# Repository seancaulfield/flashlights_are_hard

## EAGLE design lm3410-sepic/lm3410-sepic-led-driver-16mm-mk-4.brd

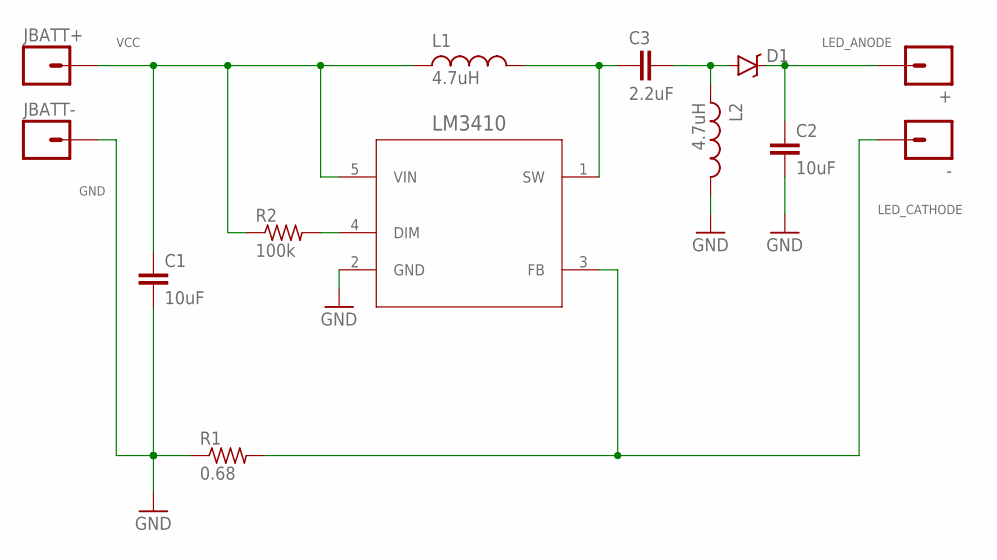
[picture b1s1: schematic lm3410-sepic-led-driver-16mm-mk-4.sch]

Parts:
+: M01PTH-1.2MM; 1X01-1.2MM
-: M01PTH-1.2MM-NS; 1X01-1.2MM-NS
C1, C2: 10uF; C0603
C3: 2.2uF; C0805
D1: MBRA140; SMA-DIODE
JBATT+: M01NOT-A-VIA-NOPE; 1X01_NOSILK_NOSTOP
JBATT-: M01NOT-A-VIA-NOPE; 1X01_NOSILK_NOSTOP
L1, L2: 4.7uH; TAIYO-YUDEN-30XX
LM3410: LM3410XMF; SOT95P285X120-5N
R1: 0.68; R1206
R2: 100k; R0603

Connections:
GND: C1.2, C2.2, JBATT-.P$1, L2.2, LM3410.2 (GND), R1.1
LED_ANODE: +.P$1, C2.1, D1.C
LED_CATHODE: -.P$1, LM3410.3 (FB), R1.2
unnamed: C3.2, D1.A, L2.1
unnamed: LM3410.4 (DIM), R2.2
SW: C3.1, L1.2, LM3410.1 (SW)
VCC: C1.1, JBATT+.P$1, L1.1, LM3410.5 (VIN), R2.1

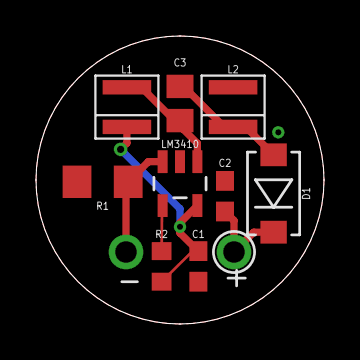
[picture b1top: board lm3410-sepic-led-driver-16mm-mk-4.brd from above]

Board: 2 copper layers, 16.0 x 16.0 mm, 13 parts (0 on the bottom side), 7 nets.

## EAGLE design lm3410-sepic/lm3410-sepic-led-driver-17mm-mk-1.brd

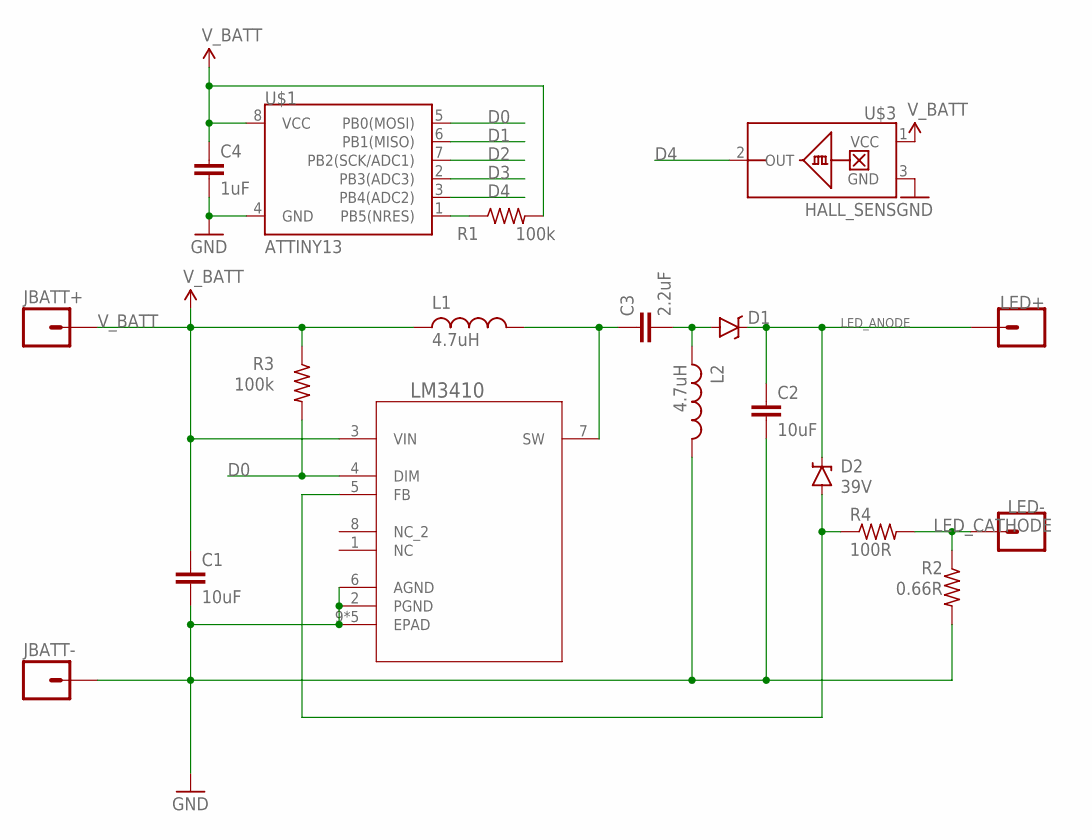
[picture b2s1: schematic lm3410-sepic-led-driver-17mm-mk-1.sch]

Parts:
C1, C2: 10uF; C0805
C3: 2.2uF; C0805
C4: 1uF; C0603
D1: BAT20J; SOD-323
D2: 39V; SOD-323
JBATT+: M01NOT-A-VIA-NOPE; 1X01_NOSILK_NOSTOP
JBATT-: M01NOT-A-VIA-NOPE; 1X01_NOSILK_NOSTOP
L1, L2: 4.7uH; TAIYO-YUDEN-30XX
LED+: M01PTH-NS-NOTSUCK; 1X01NSATALL
LED-: M01PTH-NS-NOTSUCK; 1X01NSATALL
R1, R3: 100k; R0603
R2: 0.66R; R1206
R4: 100R; R0603
U1: LM3410; SOP65P490X110-9N-A
U$1: ATTINY13; SO08
U$3: HALL_SENS; SOT23-3

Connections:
D0: R3.2, U1.4 (DIM), U$1.5 (PB0(MOSI))
D1: U$1.6 (PB1(MISO))
D2: U$1.7 (PB2(SCK/ADC1))
D3: U$1.2 (PB3(ADC3))
D4: U$1.3 (PB4(ADC2)), U$3.2 (OUT)
GND: C1.2, C2.2, C4.2, JBATT-.P$1, L2.2, R2.2, U1.2 (PGND), U1.6 (AGND), U1.9 (EPAD), U1.9@1 (EPAD), U1.9@2 (EPAD), U1.9@3 (EPAD), U1.9@4 (EPAD), U$1.4 (GND), U$3.3 (GND)
LED_ANODE: C2.1, D1.C, D2.C, LED+.1
LED_CATHODE: LED-.1, R2.1, R4.2
unnamed: C3.2, D1.A, L2.1
unnamed: R1.1, U$1.1 (PB5(NRES))
unnamed: D2.A, R4.1, U1.5 (FB)
SW: C3.1, L1.2, U1.7 (SW)
V_BATT: C1.1, C4.1, JBATT+.P$1, L1.1, R1.2, R3.1, U1.3 (VIN), U$1.8 (VCC), U$3.1 (VCC)

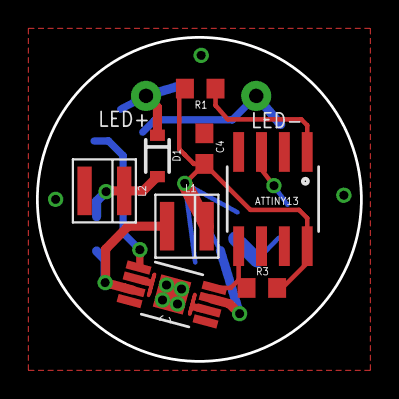
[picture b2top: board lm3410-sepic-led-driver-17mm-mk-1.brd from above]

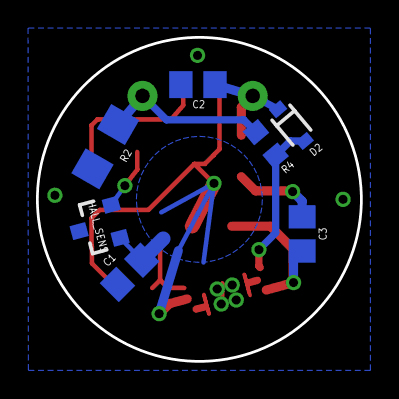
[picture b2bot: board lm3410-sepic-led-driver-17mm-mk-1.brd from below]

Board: 2 copper layers, 18.0 x 18.0 mm, 19 parts (8 on the bottom side), 10 nets.

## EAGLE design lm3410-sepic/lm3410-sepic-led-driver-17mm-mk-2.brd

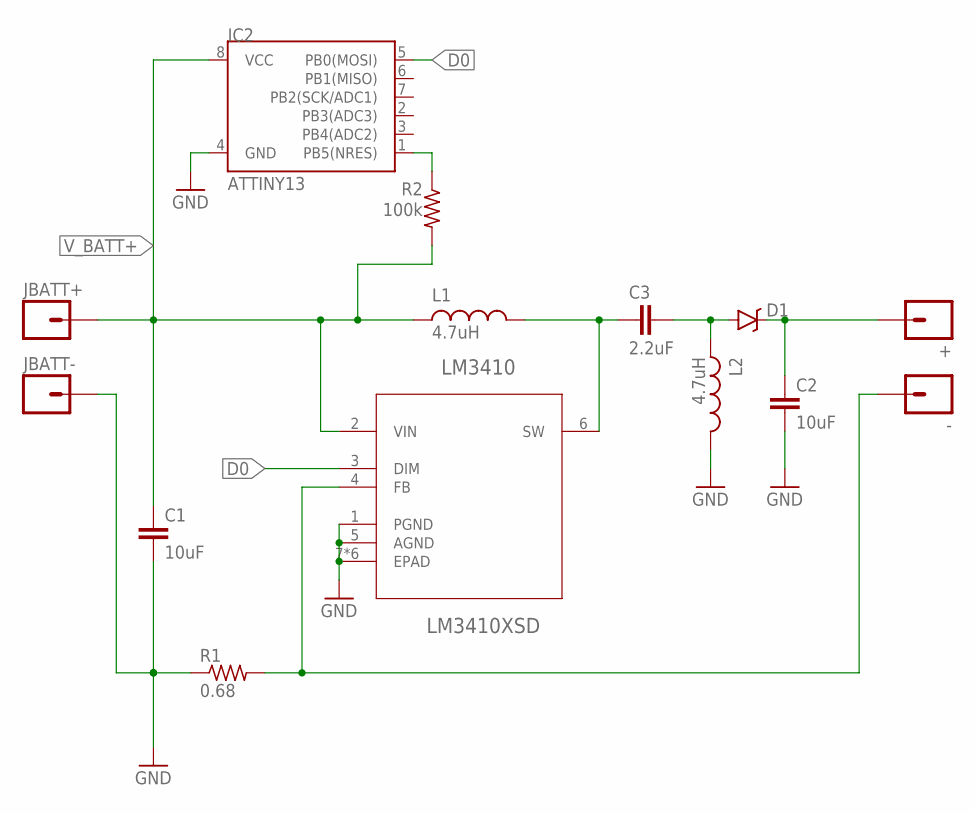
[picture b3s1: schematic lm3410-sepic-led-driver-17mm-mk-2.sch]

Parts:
+: M01PTH-KIT; 1X01-KIT
-: M01NOSILK-KIT; 1X01NS-KIT
C1, C2: 10uF; C0603
C3: 2.2uF; C0805
D1: BAT20J; SOD-323
IC2: ATTINY13; SO08
JBATT+: M01NOT-A-VIA-NOPE; 1X01_NOSILK_NOSTOP
JBATT-: M01NOT-A-VIA-NOPE; 1X01_NOSILK_NOSTOP
L1, L2: 4.7uH; INDUCTOR_2X1.6MM
LM3410: LM3410XSD; DFN300X300X80-7N
R1: 0.68; R1206
R2: 100k; R0402

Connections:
D0: IC2.5 (PB0(MOSI)), LM3410.3 (DIM)
GND: C1.2, C2.2, IC2.4 (GND), JBATT-.P$1, L2.P$2 (2), LM3410.1 (PGND), LM3410.5 (AGND), LM3410.7 (EPAD), LM3410.7@1 (EPAD), LM3410.7@2 (EPAD), LM3410.7@3 (EPAD), LM3410.7@4 (EPAD), LM3410.7@5 (EPAD), R1.1
LED_ANODE: +.1, C2.1, D1.C
unnamed: C3.2, D1.A, L2.P$1 (1)
unnamed: IC2.1 (PB5(NRES)), R2.1
unnamed: -.1, LM3410.4 (FB), R1.2
SW: C3.1, L1.P$2 (2), LM3410.6 (SW)
V_BATT+: C1.1, IC2.8 (VCC), JBATT+.P$1, L1.P$1 (1), LM3410.2 (VIN), R2.2

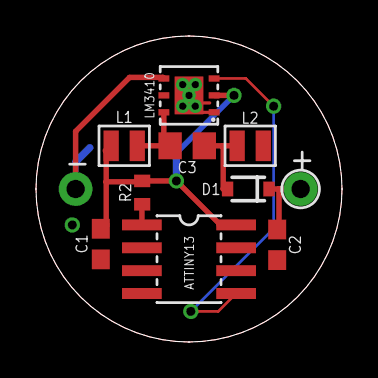
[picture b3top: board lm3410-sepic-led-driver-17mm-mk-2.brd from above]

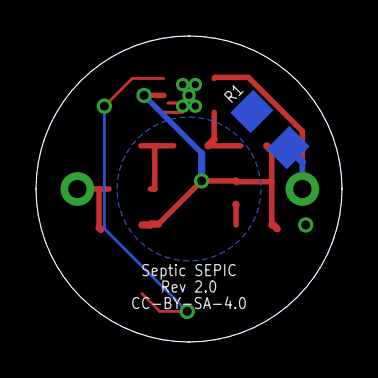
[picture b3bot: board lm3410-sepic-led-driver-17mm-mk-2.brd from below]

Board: 2 copper layers, 17.0 x 17.0 mm, 14 parts (2 on the bottom side), 8 nets.

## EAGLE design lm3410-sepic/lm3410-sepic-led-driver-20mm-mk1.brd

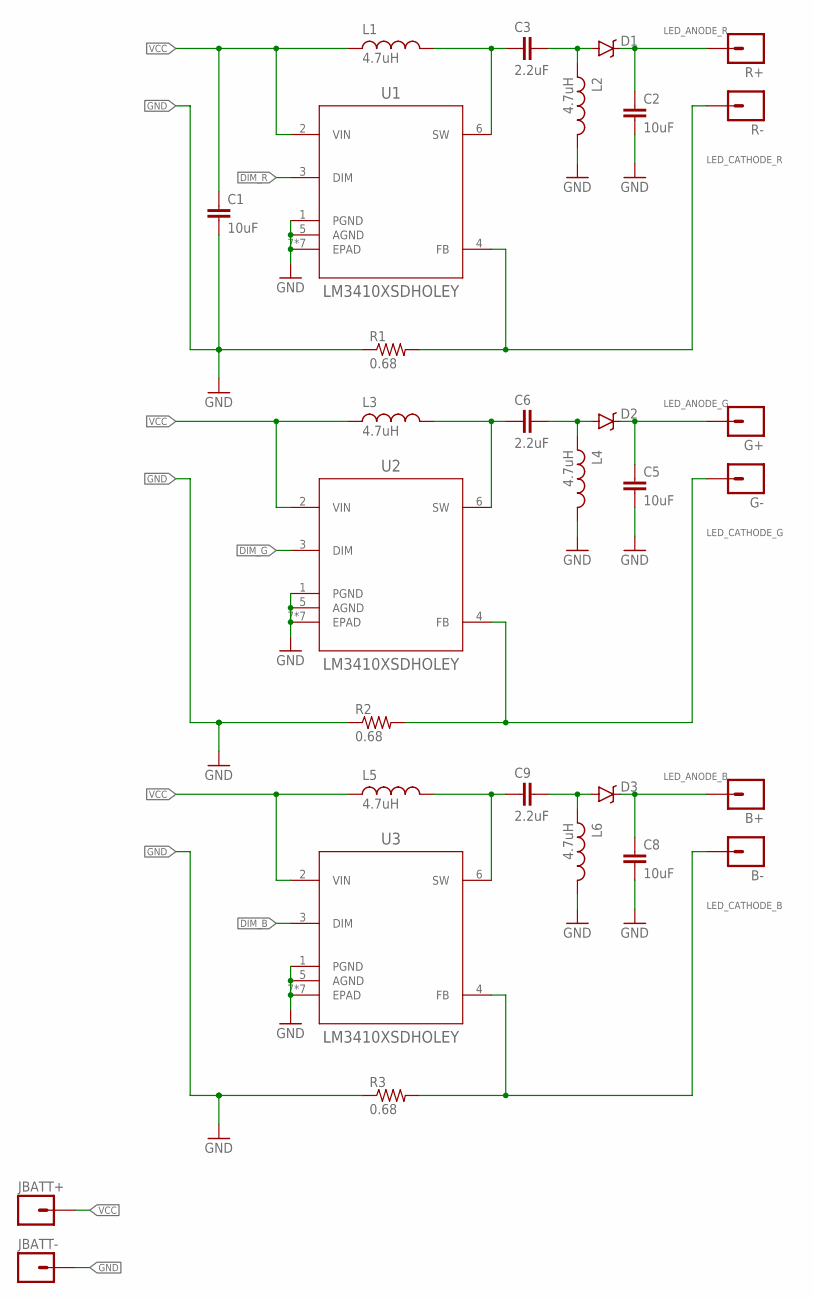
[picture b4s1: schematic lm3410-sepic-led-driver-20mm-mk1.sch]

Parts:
B+: M01PTH-1.2MM; 1X01-1.2MM
B-: M01PTH-1.2MM-NS; 1X01-1.2MM-NS
C1, C2, C5, C8: 10uF; C0603
C3, C6, C9: 2.2uF; C0805
D1, D2, D3: PMEG4005EJ; SOD-323
G+: M01PTH-1.2MM; 1X01-1.2MM
G-: M01PTH-1.2MM-NS; 1X01-1.2MM-NS
JBATT+: M01NOT-A-VIA-NOPE; 1X01_NOSILK_NOSTOP
JBATT-: M01NOT-A-VIA-NOPE; 1X01_NOSILK_NOSTOP
L1, L2, L3, L4, L5, L6: 4.7uH; INDUCTOR_2X1.6MM
R1, R2, R3: 0.68; R1206
R+: M01PTH-1.2MM; 1X01-1.2MM
R-: M01PTH-1.2MM-NS; 1X01-1.2MM-NS
U1, U2, U3: LM3410XSDHOLEY; DFN300X300X80-7N-HOLES

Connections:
DIM_B: U3.3 (DIM)
DIM_G: U2.3 (DIM)
DIM_R: U1.3 (DIM)
GND: C1.2, C2.2, C5.2, C8.2, JBATT-.P$1, L2.P$2 (2), L4.P$2 (2), L6.P$2 (2), R1.1, R2.1, R3.1, U1.1 (PGND), U1.5 (AGND), U1.7 (EPAD), U1.7@1 (EPAD), U1.7@2 (EPAD), U1.7@3 (EPAD), U1.7@4 (EPAD), U1.7@5 (EPAD), U1.7@6 (EPAD), U2.1 (PGND), U2.5 (AGND), U2.7 (EPAD), U2.7@1 (EPAD), U2.7@2 (EPAD), U2.7@3 (EPAD), U2.7@4 (EPAD), U2.7@5 (EPAD), U2.7@6 (EPAD), U3.1 (PGND), U3.5 (AGND), U3.7 (EPAD), U3.7@1 (EPAD), U3.7@2 (EPAD), U3.7@3 (EPAD), U3.7@4 (EPAD), U3.7@5 (EPAD), U3.7@6 (EPAD)
LED_ANODE_B: B+.P$1, C8.1, D3.C
LED_ANODE_G: C5.1, D2.C, G+.P$1
LED_ANODE_R: C2.1, D1.C, R+.P$1
LED_CATHODE_B: B-.P$1, R3.2, U3.4 (FB)
LED_CATHODE_G: G-.P$1, R2.2, U2.4 (FB)
LED_CATHODE_R: R1.2, R-.P$1, U1.4 (FB)
unnamed: C3.2, D1.A, L2.P$1 (1)
unnamed: C6.2, D2.A, L4.P$1 (1)
unnamed: C9.2, D3.A, L6.P$1 (1)
SW: C3.1, L1.P$2 (2), U1.6 (SW)
SW1: C6.1, L3.P$2 (2), U2.6 (SW)
SW2: C9.1, L5.P$2 (2), U3.6 (SW)
VCC: C1.1, JBATT+.P$1, L1.P$1 (1), L3.P$1 (1), L5.P$1 (1), U1.2 (VIN), U2.2 (VIN), U3.2 (VIN)

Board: 2 copper layers, 30 parts (3 on the bottom side), 14 nets, no tracks yet.

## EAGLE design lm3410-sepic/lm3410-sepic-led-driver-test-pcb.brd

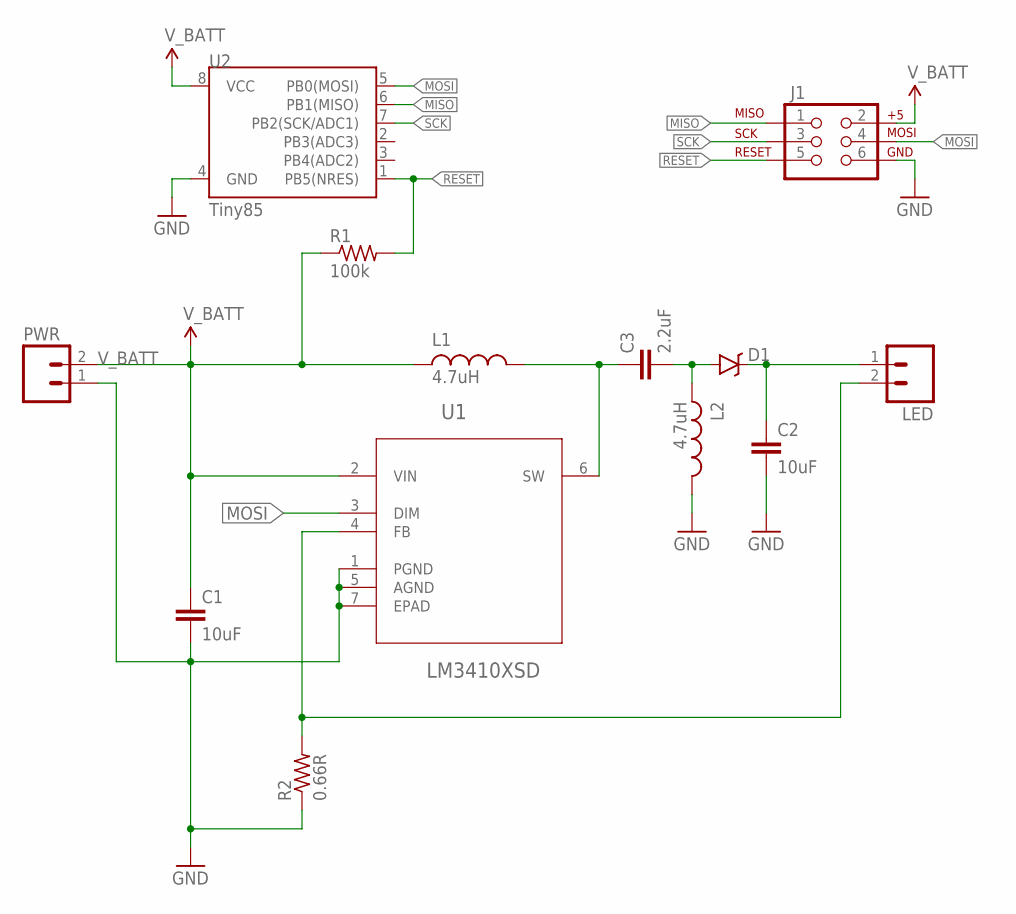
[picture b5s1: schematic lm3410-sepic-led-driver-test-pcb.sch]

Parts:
C1, C2: 10uF; C0805
C3: 2.2uF; C0805
D1: BAT20J; SOD-323
J1: AVR_SPI_PRG_6PTH; 2X3
L1, L2: 4.7uH; INDUCTOR_2X1.6MM
LED: M02PTH; 1X02
PWR: M02PTH; 1X02
R1: 100k; R0603
R2: 0.66R; R1206
U1: LM3410XSD; DFN300X300X80-7N
U2: Tiny85; SO08-EIAJ

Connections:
GND: C1.2, C2.2, J1.6, L2.P$2 (2), PWR.1, R2.1, U1.1 (PGND), U1.5 (AGND), U1.7 (EPAD), U2.4 (GND)
LED_ANODE: C2.1, D1.C, LED.1
MISO: J1.1, U2.6 (PB1(MISO))
MOSI: J1.4, U1.3 (DIM), U2.5 (PB0(MOSI))
unnamed: C3.2, D1.A, L2.P$1 (1)
unnamed: LED.2, R2.2, U1.4 (FB)
RESET: J1.5, R1.2, U2.1 (PB5(NRES))
SCK: J1.3, U2.7 (PB2(SCK/ADC1))
SW: C3.1, L1.P$2 (2), U1.6 (SW)
V_BATT: C1.1, J1.2, L1.P$1 (1), PWR.2, R1.1, U1.2 (VIN), U2.8 (VCC)

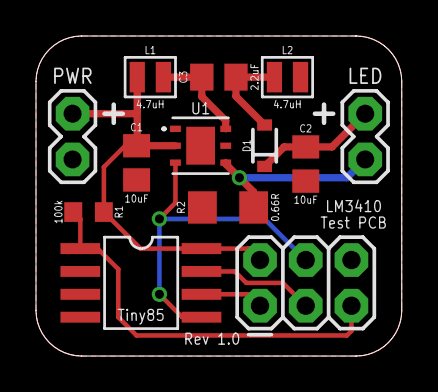
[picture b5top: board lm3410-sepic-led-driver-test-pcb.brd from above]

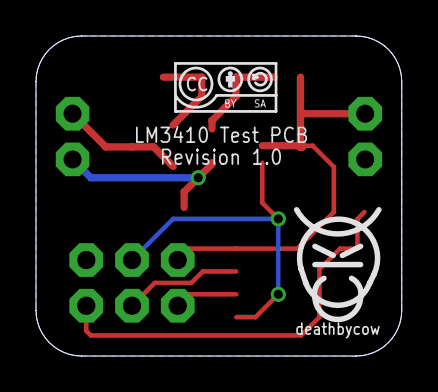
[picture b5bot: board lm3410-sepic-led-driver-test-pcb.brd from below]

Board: 2 copper layers, 20.3 x 17.8 mm, 15 parts (2 on the bottom side), 10 nets.

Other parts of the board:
U$1: COW_SMALL
U$2: CC-BY-SA-4.0-NO-URL

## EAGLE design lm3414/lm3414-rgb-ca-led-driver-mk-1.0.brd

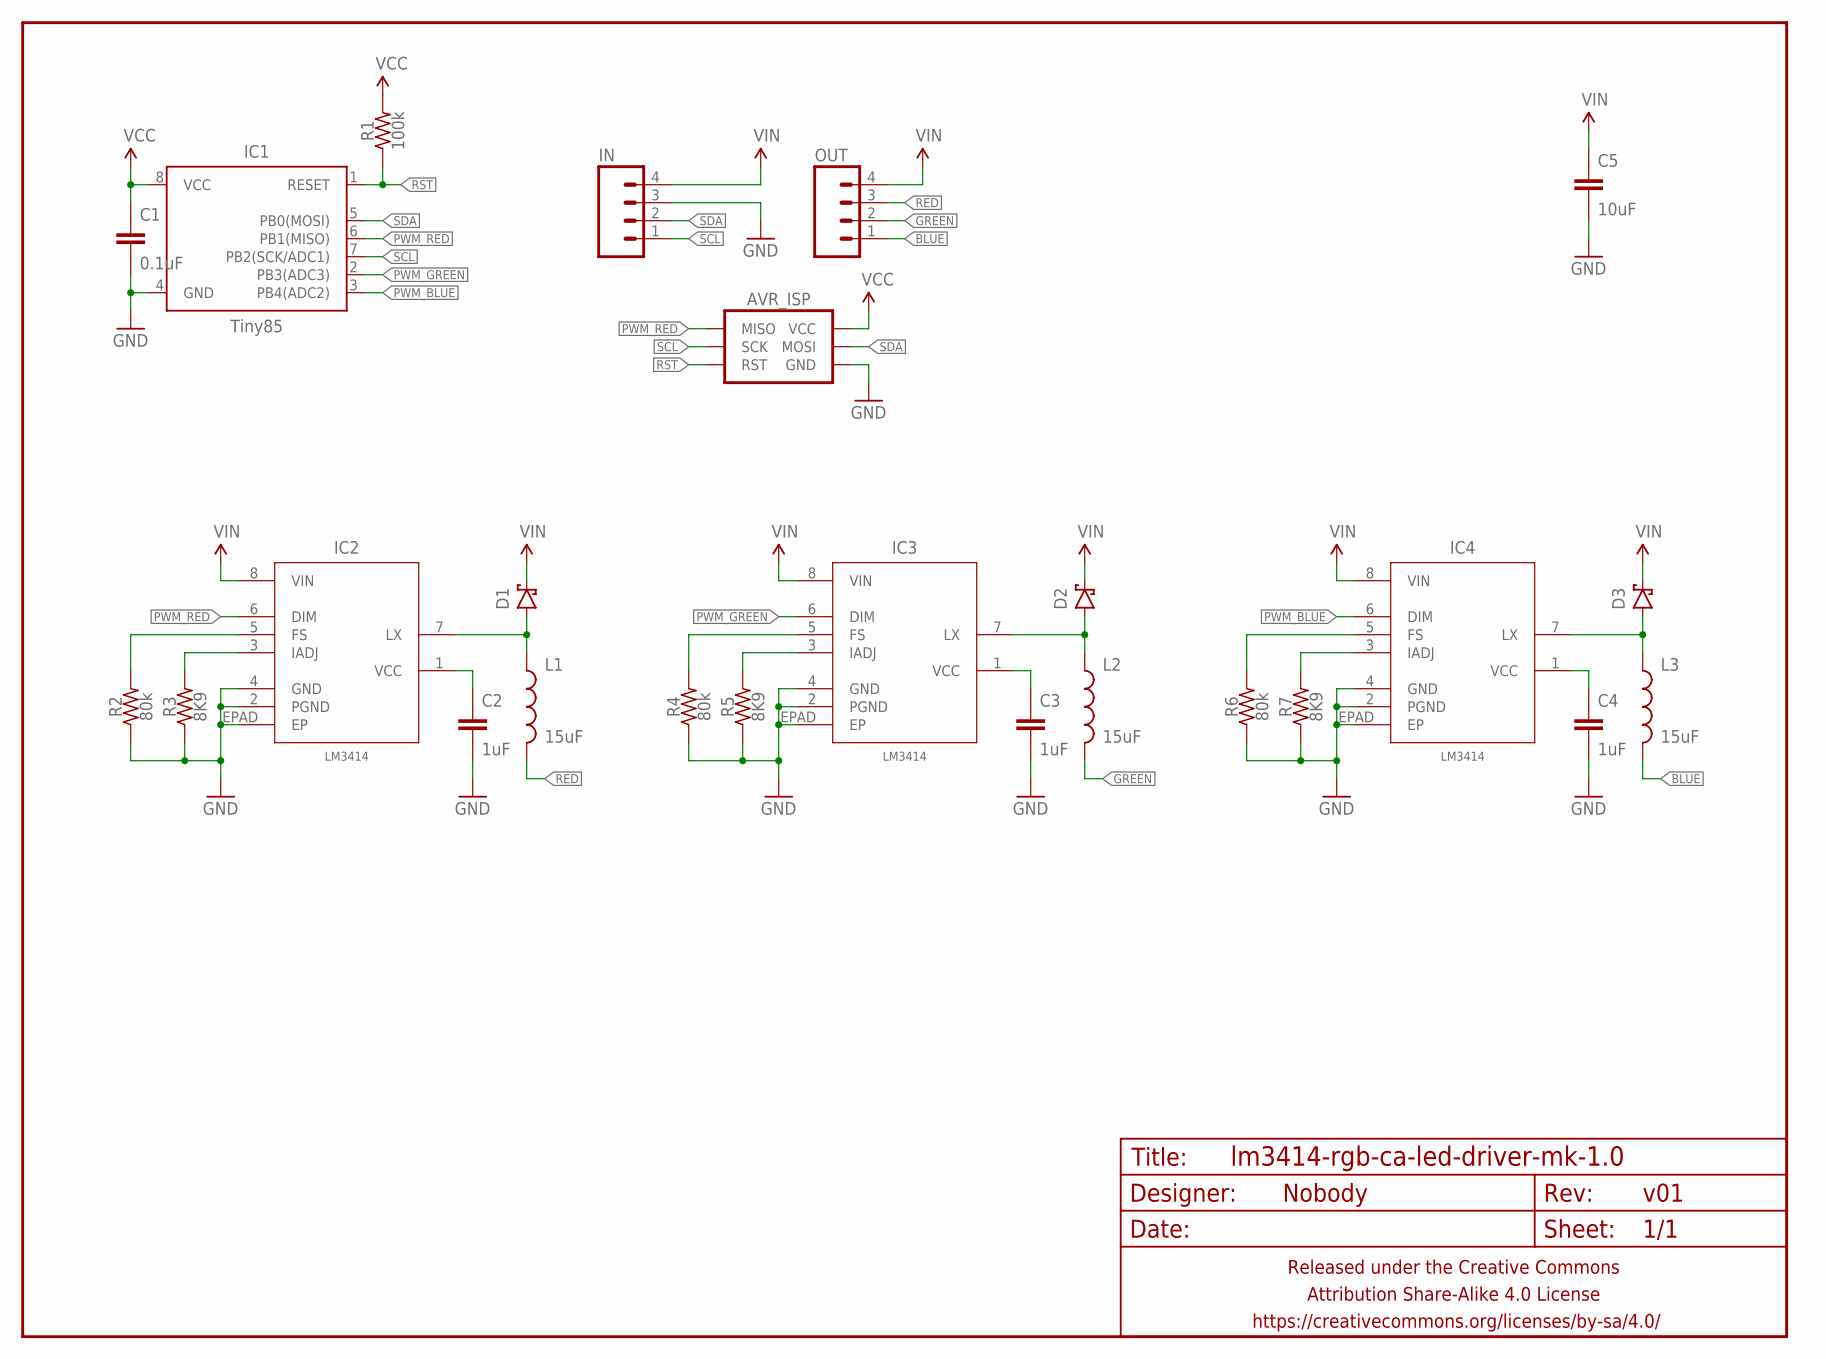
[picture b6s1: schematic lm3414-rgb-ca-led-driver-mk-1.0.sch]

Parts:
AVR_ISP: AVR_SPI_PRG_6TESTPOINTS; 2X3_TEST_POINTS
C1: 0.1uF; C0603
C2, C3, C4: 1uF; C0603
C5: 10uF; C1206
D1, D2, D3: DIODE-SCHOTTKYSMA; SMA-DIODE-SCHOTTKY
FRAME1: FRAME-LETTERNO_PACKAGE; DUMMY
IC1: Tiny85; SO08-EIAJ
IC2, IC3, IC4: LM3414; SO08-PAD
IN: M04PTH; 1X04-PTH-VERT
L1, L2, L3: 15uF; TAIYO-YUDEN-6X6X2.8
OUT: M04PTH; 1X04-PTH-VERT
R1: 100k; R0603
R2, R4, R6: 80k; R0603
R3, R5, R7: 8K9; R0603

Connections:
BLUE: L3.2, OUT.1
GND: AVR_ISP.6 (GND), C1.2, C2.2, C3.2, C4.2, C5.2, IC1.4 (GND), IC2.2 (PGND), IC2.4 (GND), IC2.EPAD (EP), IC3.2 (PGND), IC3.4 (GND), IC3.EPAD (EP), IC4.2 (PGND), IC4.4 (GND), IC4.EPAD (EP), IN.3, R2.1, R3.1, R4.1, R5.1, R6.1, R7.1
GREEN: L2.2, OUT.2
unnamed: IC2.3 (IADJ), R3.2
unnamed: IC2.5 (FS), R2.2
unnamed: IC3.3 (IADJ), R5.2
unnamed: C2.1, IC2.1 (VCC)
unnamed: IC3.5 (FS), R4.2
unnamed: D1.A, IC2.7 (LX), L1.1
unnamed: C3.1, IC3.1 (VCC)
unnamed: D2.A, IC3.7 (LX), L2.1
unnamed: IC4.3 (IADJ), R7.2
unnamed: IC4.5 (FS), R6.2
unnamed: C4.1, IC4.1 (VCC)
unnamed: D3.A, IC4.7 (LX), L3.1
PWM_BLUE: IC1.3 (PB4(ADC2)), IC4.6 (DIM)
PWM_GREEN: IC1.2 (PB3(ADC3)), IC3.6 (DIM)
PWM_RED: AVR_ISP.1 (MISO), IC1.6 (PB1(MISO)), IC2.6 (DIM)
RED: L1.2, OUT.3
RST: AVR_ISP.5 (RST), IC1.1 (RESET), R1.1
SCL: AVR_ISP.3 (SCK), IC1.7 (PB2(SCK/ADC1)), IN.1
SDA: AVR_ISP.4 (MOSI), IC1.5 (PB0(MOSI)), IN.2
VCC: AVR_ISP.2 (VCC), C1.1, IC1.8 (VCC), R1.2
VIN: C5.1, D1.C, D2.C, D3.C, IC2.8 (VIN), IC3.8 (VIN), IC4.8 (VIN), IN.4, OUT.4

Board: 2 copper layers, 26 parts (1 on the bottom side), 24 nets, no tracks yet.

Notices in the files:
parts and their libraries:
SparkFun-Aesthetics: Licensing: Creative Commons ShareAlike 4.0 International - https://creativecommons.org/licenses/by-sa/4.0
A_butts: Released under the Creative Commons Attribution Share-Alike 4.0 License
A_butts: https://creativecommons.org/licenses/by-sa/4.0
